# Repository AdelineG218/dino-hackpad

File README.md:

# dino-hackpad
A macropad in the shape of a dinosaur for HackClub's Hackpad

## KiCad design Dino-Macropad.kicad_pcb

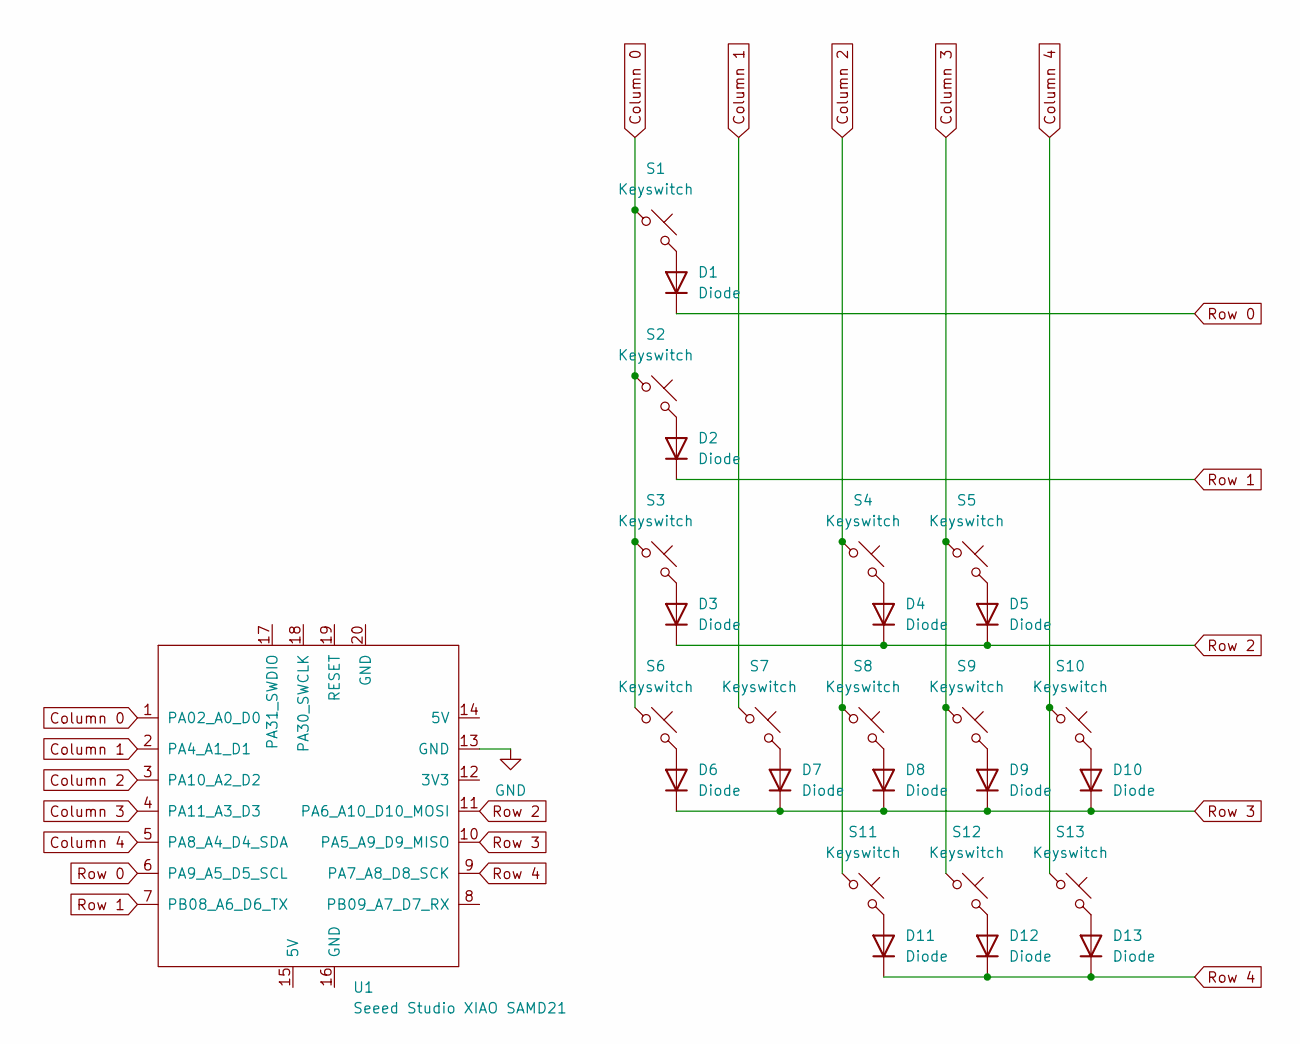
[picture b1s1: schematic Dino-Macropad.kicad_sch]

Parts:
D1, D2, D3, D4, D5, D6, D7, D8, D9, D10, D11, D12, D13: Diode; Diode_DO-35
S1, S2, S3, S4, S5, S6, S8, S9, S10, S11, S12, S13: Keyswitch; SW_Cherry_MX_1.00u_PCB
S7: Keyswitch; SW_Cherry_MX_2.00u_PCB
U1: Seeed Studio XIAO SAMD21; XIAO-Generic-Hybrid-14P-2.54-21X17.8MM

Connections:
Column 0: S1.1, S2.1, S3.1, S6.1, U1.1 (PA02_A0_D0)
Column 1: S7.1, U1.2 (PA4_A1_D1)
Column 2: S4.1, S8.1, S11.1, U1.3 (PA10_A2_D2)
Column 3: S5.1, S9.1, S12.1, U1.4 (PA11_A3_D3)
Column 4: S10.1, S13.1, U1.5 (PA8_A4_D4_SDA)
GND: U1.13 (GND)
unnamed: D1.2 (A), S1.2
unnamed: D2.2 (A), S2.2
unnamed: D3.2 (A), S3.2
unnamed: D4.2 (A), S4.2
unnamed: D5.2 (A), S5.2
unnamed: D6.2 (A), S6.2
unnamed: D7.2 (A), S7.2
unnamed: D8.2 (A), S8.2
unnamed: D9.2 (A), S9.2
unnamed: D10.2 (A), S10.2
unnamed: D11.2 (A), S11.2
unnamed: D12.2 (A), S12.2
unnamed: D13.2 (A), S13.2
Row 0: D1.1 (K), U1.6 (PA9_A5_D5_SCL)
Row 1: D2.1 (K), U1.7 (PB08_A6_D6_TX)
Row 2: D3.1 (K), D4.1 (K), D5.1 (K), U1.11 (PA6_A10_D10_MOSI)
Row 3: D6.1 (K), D7.1 (K), D8.1 (K), D9.1 (K), D10.1 (K), U1.10 (PA5_A9_D9_MISO)
Row 4: D11.1 (K), D12.1 (K), D13.1 (K), U1.9 (PA7_A8_D8_SCK)

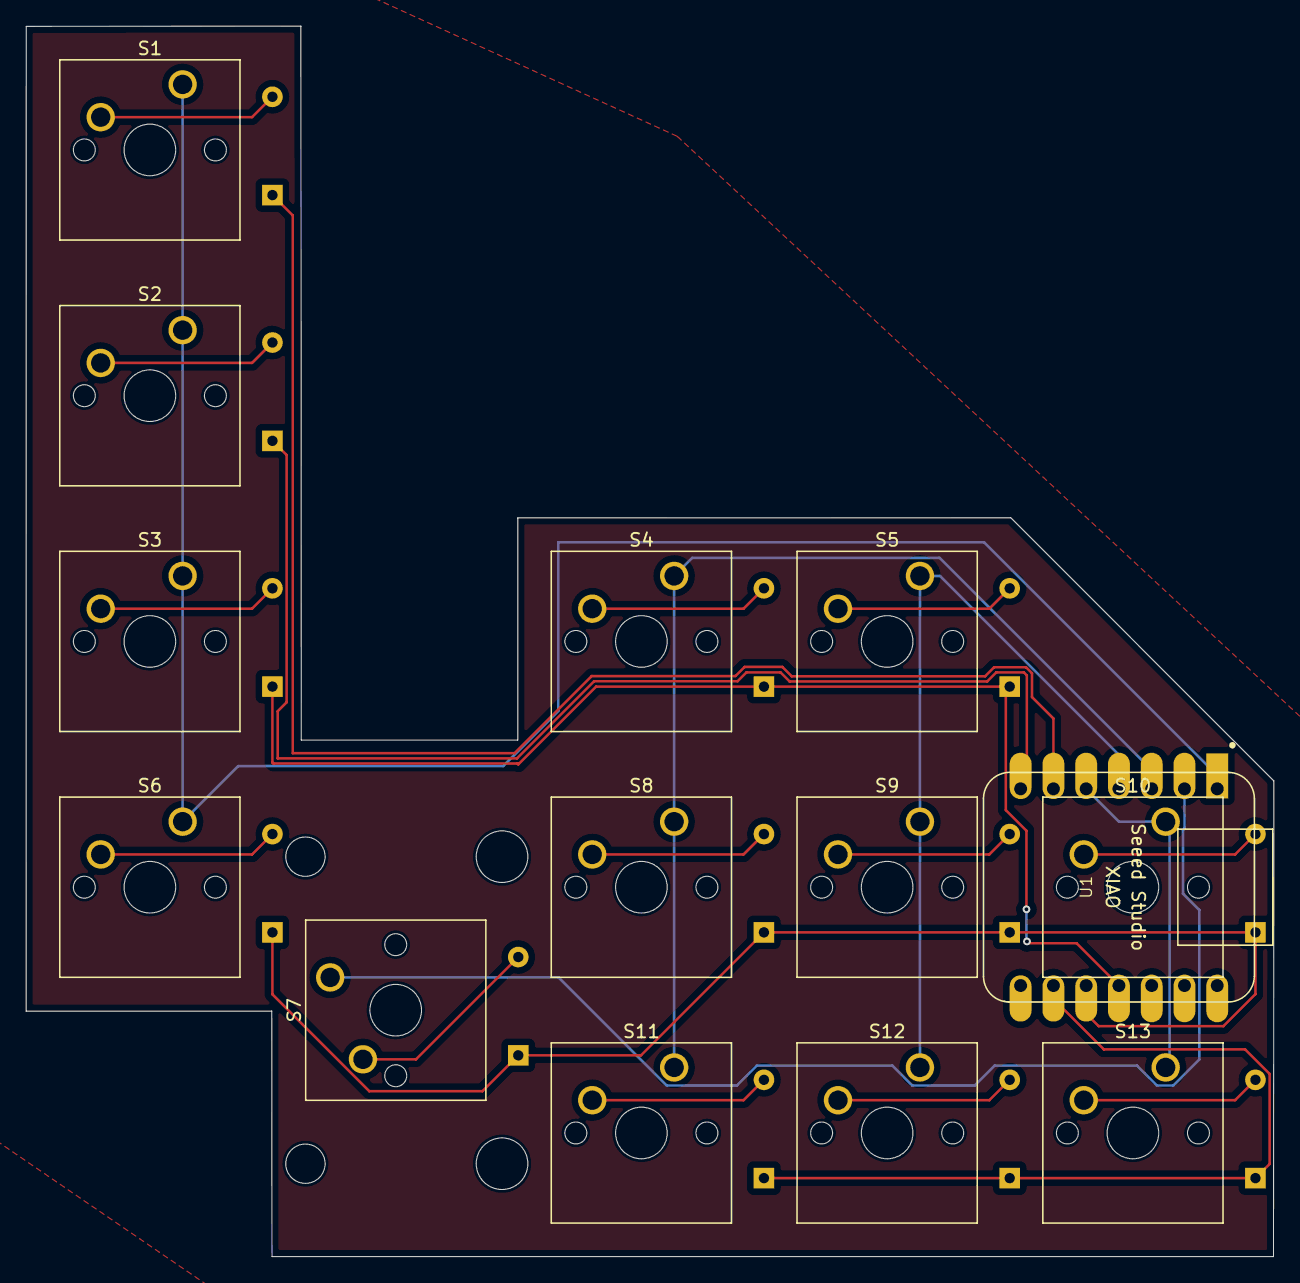
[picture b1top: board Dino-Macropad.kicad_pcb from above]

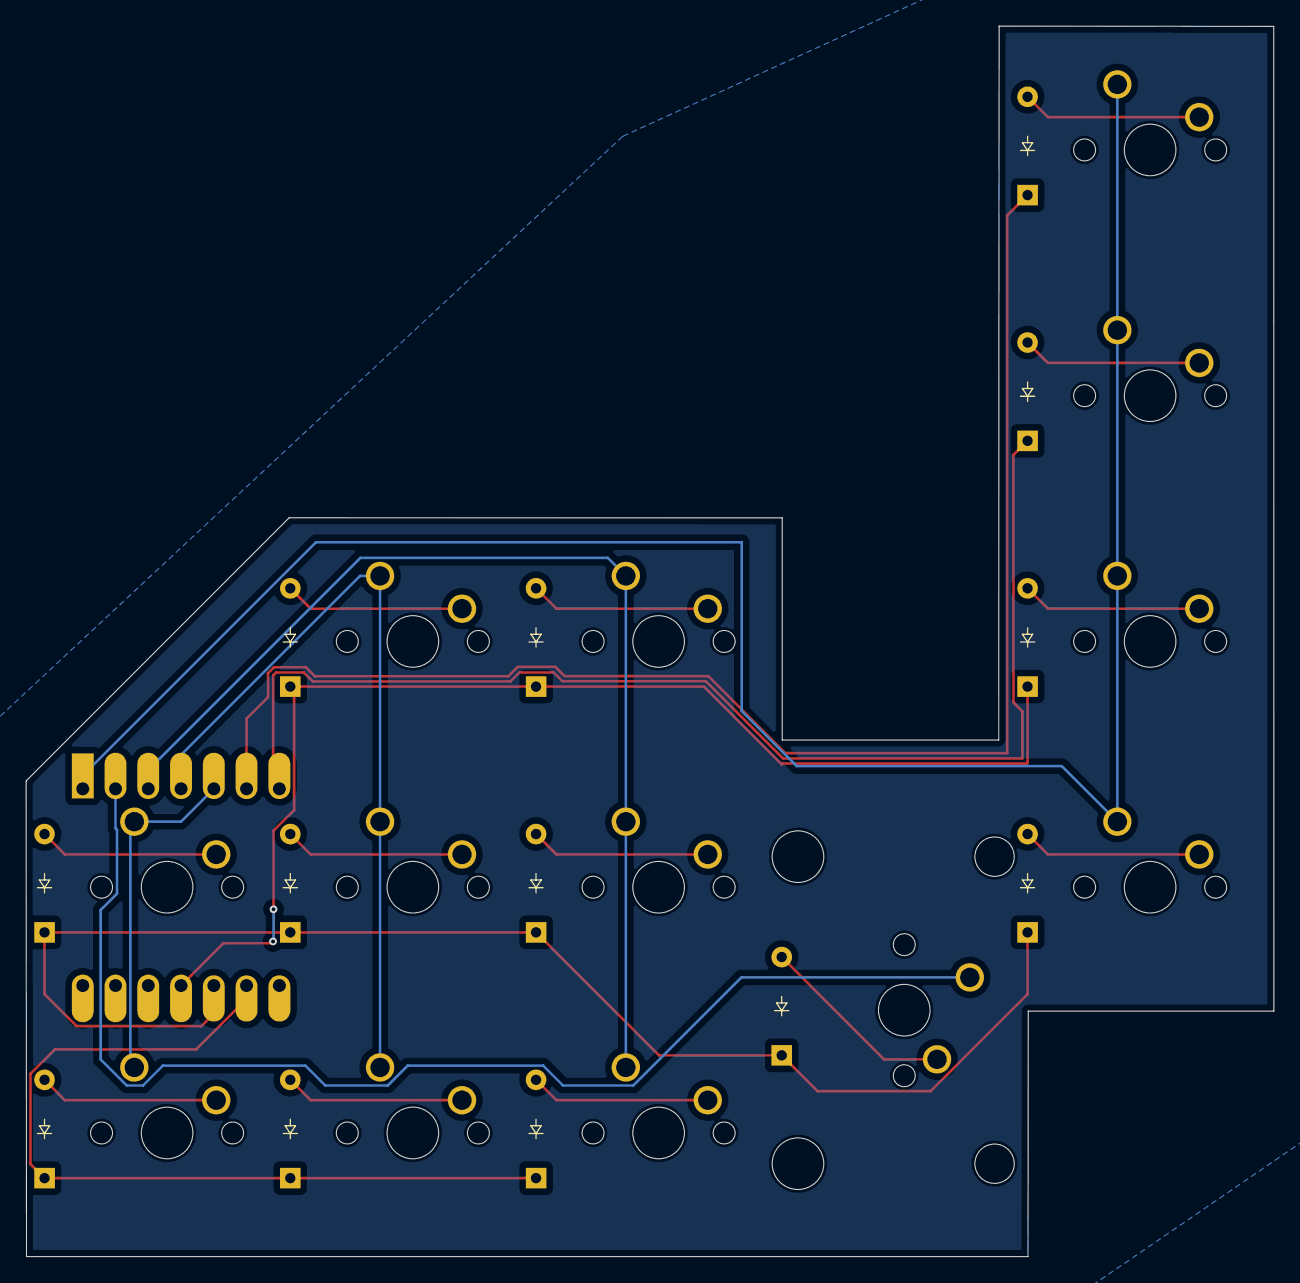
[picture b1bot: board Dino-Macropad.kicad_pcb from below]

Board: 2 copper layers, 96.7 x 95.4 mm, 27 parts (13 on the bottom side), 23 nets.

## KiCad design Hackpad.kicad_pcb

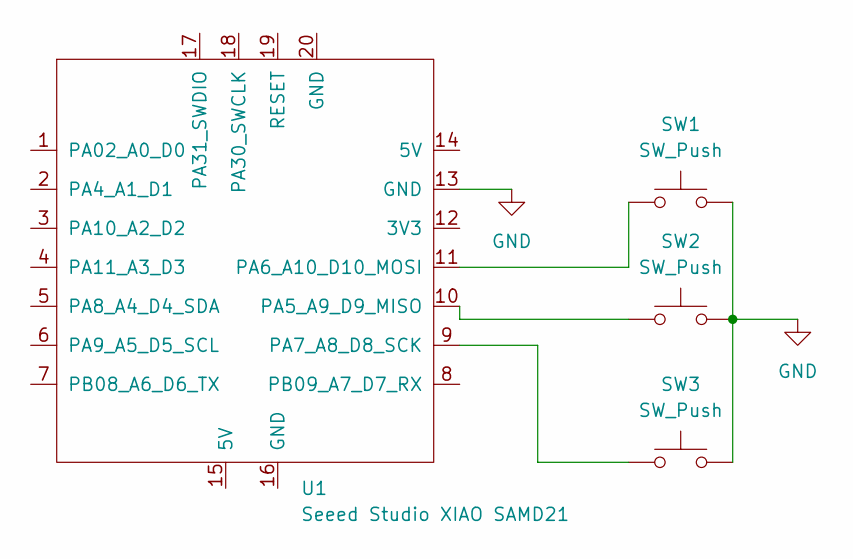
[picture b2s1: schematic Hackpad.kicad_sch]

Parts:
SW1, SW2, SW3: SW_Push; SW_Cherry_MX_1.00u_PCB
U1: Seeed Studio XIAO SAMD21; XIAO-Generic-Hybrid-14P-2.54-21X17.8MM

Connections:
GND: SW1.2, SW2.2, SW3.2, U1.13 (GND)
unnamed: SW2.1, U1.10 (PA5_A9_D9_MISO)
unnamed: SW1.1, U1.11 (PA6_A10_D10_MOSI)
unnamed: SW3.1, U1.9 (PA7_A8_D8_SCK)

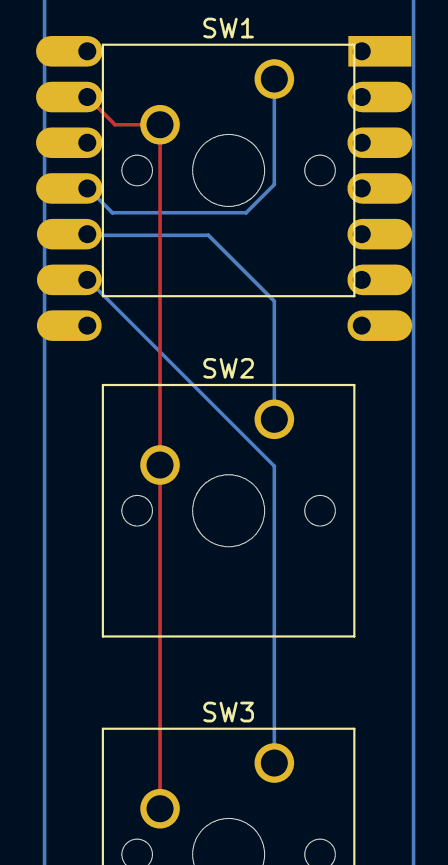
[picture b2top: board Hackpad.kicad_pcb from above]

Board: 2 copper layers, 4 parts (1 on the bottom side), 4 nets.

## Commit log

2025-06-05 original files
2025-06-05 adding original dino hackpad files from previously abandoned board
2025-06-05 6/4 journal update
2025-06-05 updated the journal entry to have the time
